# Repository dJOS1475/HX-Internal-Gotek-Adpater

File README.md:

# HX-Internal-Gotek-Adpater
Tandy 1000 HX, RL, RLX & RSX Internal Gotek Adpater

This Tandy 1000 Internal Gotek Adapter allows you to use Gotek Virtual Floppy Drives with the Tandy 1000 HX which sends power over the Floppy cable and uses a non-standard pin-out.

I made these because many folks wanted to use Gotek Virtual Floppy Drives with their Tandy's but due to the non-standard power-over-cable-design were unable to.

I highly recommend using the free FlashFloppy Firmware on Gotek Drives as the stock FW is quite poor. On my TL/2, I found that the FlashFloppy FF.CFG file needs the "pin34" option set to "chg" to enable Disk Change detection.

My Store can be found here: https://www.tindie.com/stores/CyberneticSys/

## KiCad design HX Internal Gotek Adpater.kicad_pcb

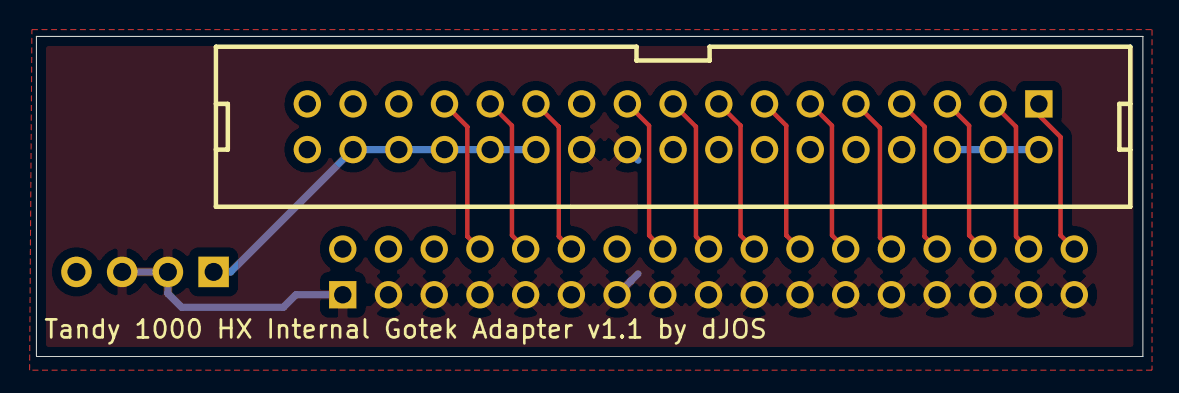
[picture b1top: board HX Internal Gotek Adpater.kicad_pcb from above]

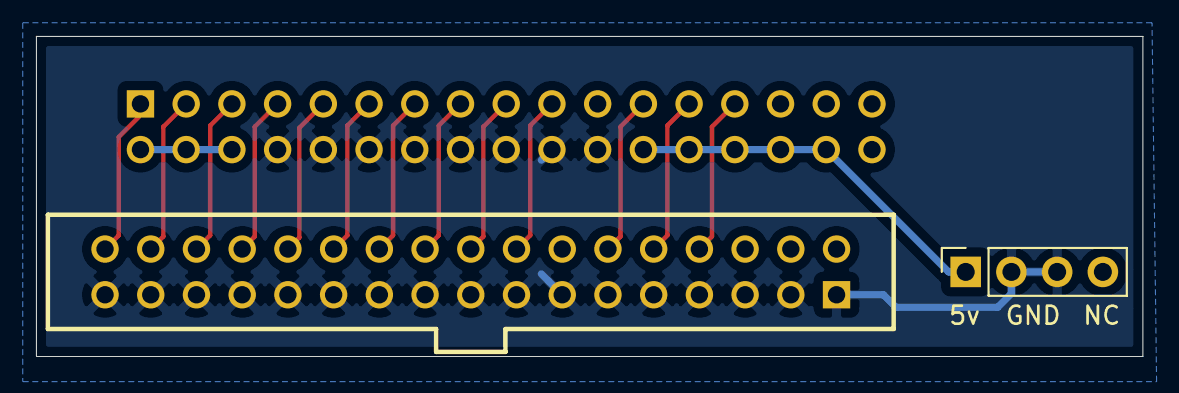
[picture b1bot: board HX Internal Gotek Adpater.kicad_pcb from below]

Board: 2 copper layers, 61.5 x 17.8 mm, 3 parts (2 on the bottom side), 16 nets.

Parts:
J1: Conn_02x17_Odd_Even; IDC34M
J2: Conn_02x17_Odd_Even; IDC34F
J3: Conn_01x04_Female; PinSocket_1x04_P2.54mm_Vertical

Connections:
/5V: J1.24, J1.26, J1.28, J1.30, J1.32, J3.1
/12V: J1.2, J1.4, J1.6
/DCHG: J1.1, J2.34
/DIR: J1.17, J2.18
/DS0: J1.25, J2.10
/DS2: J1.23, J2.12
/GND: J1.8, J1.10, J1.12, J1.14, J1.16, J1.18, J1.20, J1.22, J2.1, J2.3, J2.5, J2.7, J2.9, J2.11, J2.13, J2.15, J2.17, J2.19, J2.21, J2.23, J2.25, J2.27, J2.29, J2.31, J2.33, J3.2, J3.3
/Index: J1.27, J2.8
/MTRON: J1.19, J2.16
/RDDATA: J1.5, J2.30
/SIDESELECT: J1.3, J2.32
/STEP: J1.15, J2.20
/TRK0: J1.9, J2.26
/WEN: J1.11, J2.24
/WRDATA: J1.13, J2.22
/WRPRT: J1.7, J2.28
